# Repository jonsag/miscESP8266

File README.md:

# misc ESP8266

Tests and minor projects

## esp-01_ch340g

To program  

* Insert in programmer board  
* Hold down flash button
* Toggle reset button  
* Release flash button

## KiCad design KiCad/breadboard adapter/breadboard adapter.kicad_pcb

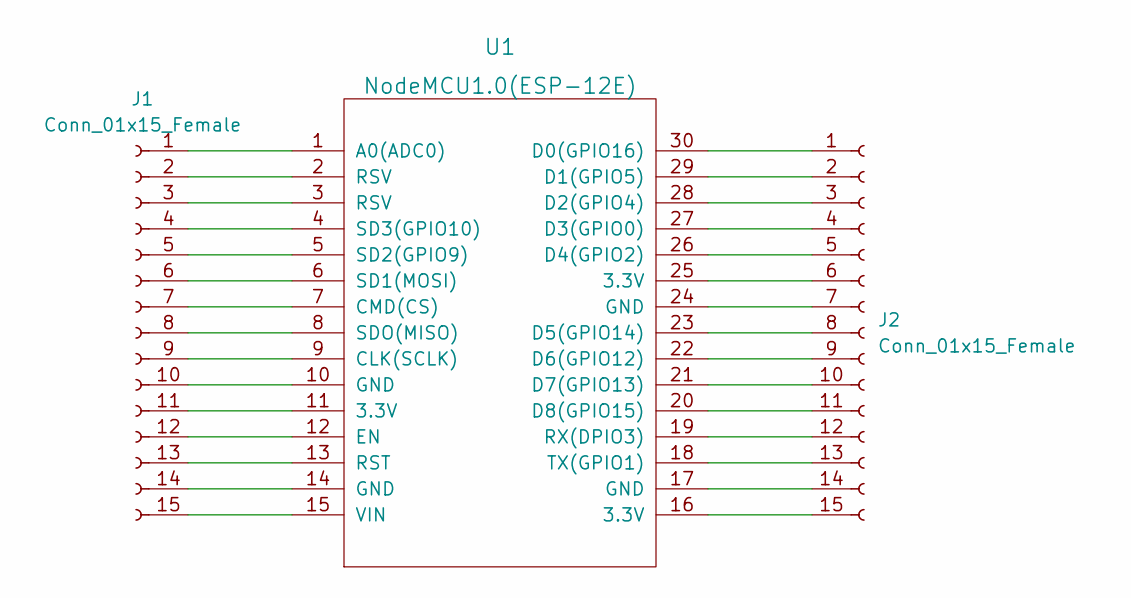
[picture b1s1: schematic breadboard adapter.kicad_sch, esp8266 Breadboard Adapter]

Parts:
J1, J2: Conn_01x15_Female; PinHeader_1x15_P2.54mm_Vertical
U1: NodeMCU1.0(ESP-12E); NodeMCU-LoLinV3_w_pinsockets_large

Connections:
unnamed: J1.1, U1.1 (A0(ADC0))
unnamed: J1.2, U1.2 (RSV)
unnamed: J1.3, U1.3 (RSV)
unnamed: J1.4, U1.4 (SD3(GPIO10))
unnamed: J1.5, U1.5 (SD2(GPIO9))
unnamed: J1.6, U1.6 (SD1(MOSI))
unnamed: J1.7, U1.7 (CMD(CS))
unnamed: J1.8, U1.8 (SDO(MISO))
unnamed: J1.9, U1.9 (CLK(SCLK))
unnamed: J1.10, U1.10 (GND)
unnamed: J1.11, U1.11 (3.3V)
unnamed: J1.12, U1.12 (EN)
unnamed: J1.13, U1.13 (RST)
unnamed: J1.14, U1.14 (GND)
unnamed: J1.15, U1.15 (VIN)
unnamed: J2.1, U1.30 (D0(GPIO16))
unnamed: J2.2, U1.29 (D1(GPIO5))
unnamed: J2.3, U1.28 (D2(GPIO4))
unnamed: J2.4, U1.27 (D3(GPIO0))
unnamed: J2.5, U1.26 (D4(GPIO2))
unnamed: J2.6, U1.25 (3.3V)
unnamed: J2.7, U1.24 (GND)
unnamed: J2.8, U1.23 (D5(GPIO14))
unnamed: J2.9, U1.22 (D6(GPIO12))
unnamed: J2.10, U1.21 (D7(GPIO13))
unnamed: J2.11, U1.20 (D8(GPIO15))
unnamed: J2.12, U1.19 (RX(DPIO3))
unnamed: J2.13, U1.18 (TX(GPIO1))
unnamed: J2.14, U1.17 (GND)
unnamed: J2.15, U1.16 (3.3V)

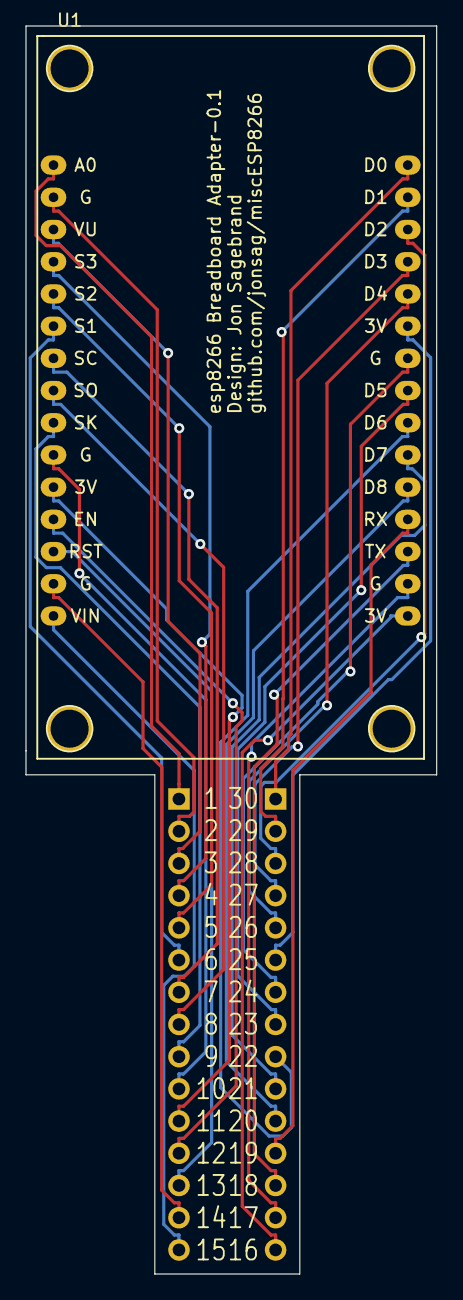
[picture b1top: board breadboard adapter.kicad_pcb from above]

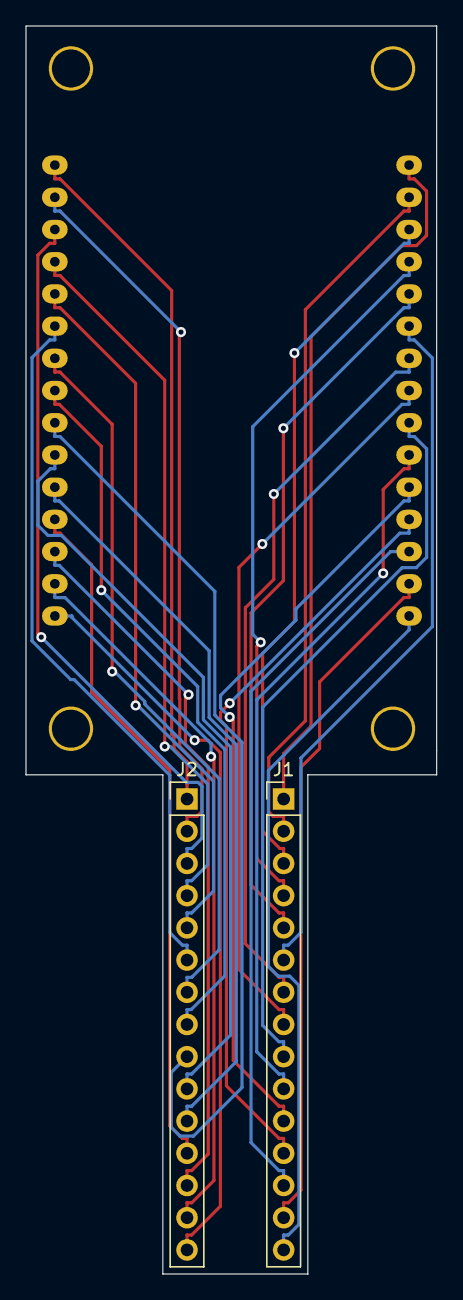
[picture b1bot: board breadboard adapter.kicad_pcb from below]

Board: 2 copper layers, 32.4 x 98.4 mm, 3 parts (2 on the bottom side), 30 nets.

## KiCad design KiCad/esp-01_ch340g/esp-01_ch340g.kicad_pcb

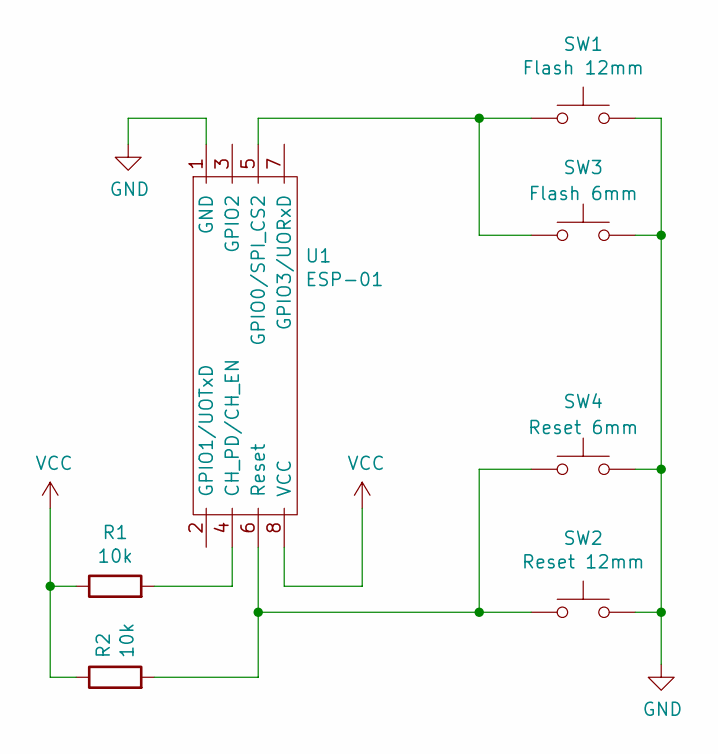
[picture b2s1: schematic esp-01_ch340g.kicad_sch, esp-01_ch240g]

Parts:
R1, R2: 10k; R_Axial_DIN0207_L6.3mm_D2.5mm_P10.16mm_Horizontal_larger_pa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
SW1: Flash 12mm; SW_PUSH-12mm_large
SW2: Reset 12mm; SW_PUSH-12mm_large
SW3: Flash 6mm; SW_PUSH_6mm_large
SW4: Reset 6mm; SW_PUSH_6mm_large
U1: ESP-01; ESP-01_w_pin_socket_large

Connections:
GND: SW1.2, SW2.2, SW3.2, SW4.2, U1.1 (GND)
unnamed: R1.2, U1.4 (CH_PD/CH_EN)
unnamed: R2.2, SW2.1, SW4.1, U1.6 (Reset)
unnamed: SW1.1, SW3.1, U1.5 (GPIO0/SPI_CS2)
VCC: R1.1, R2.1, U1.8 (VCC)

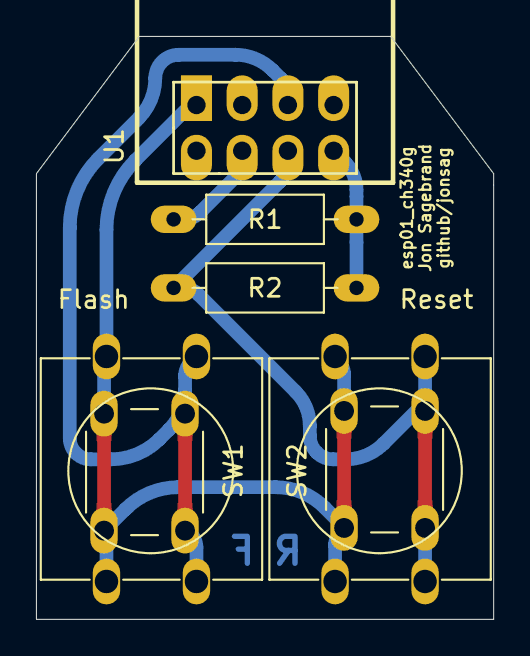
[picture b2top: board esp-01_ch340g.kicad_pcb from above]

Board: 2 copper layers, 25.4 x 32.4 mm, 7 parts (0 on the bottom side), 5 nets.

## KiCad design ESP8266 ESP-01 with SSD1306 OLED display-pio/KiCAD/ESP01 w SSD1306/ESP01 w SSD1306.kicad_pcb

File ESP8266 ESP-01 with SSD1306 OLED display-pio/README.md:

# Links

[https://simple-circuit.com/esp-01-esp8266-ssd1306-oled-i2c-mode/](ESP8266 ESP-01 with SSD1306 OLED display)
[https://richard-ramos.github.io/esp-01-oled/](Adding a OLED screen to the ESP-01)

[http://javl.github.io/image2cpp/](image2cpp)

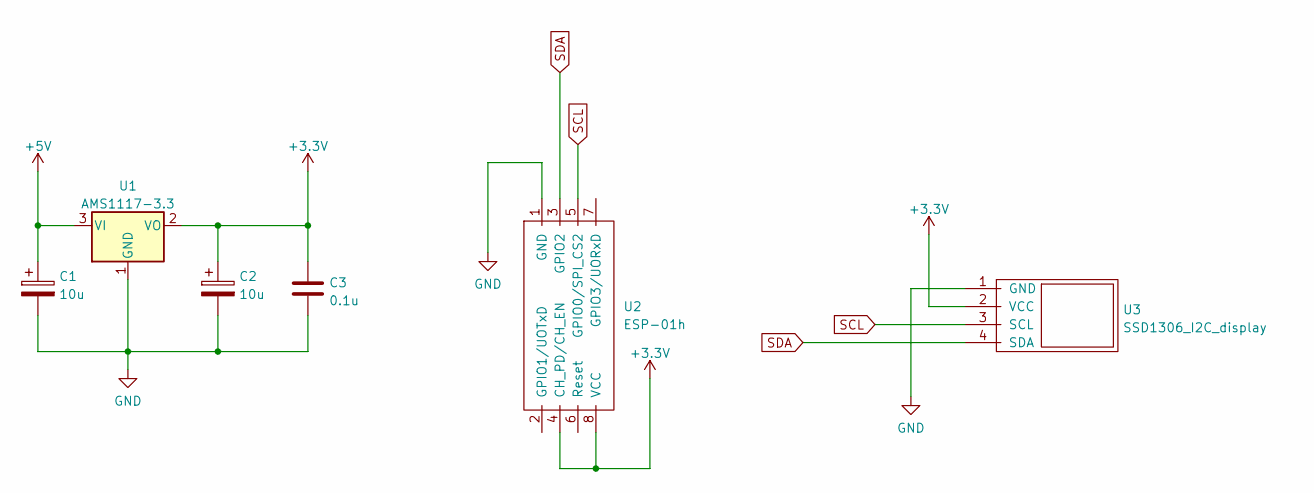
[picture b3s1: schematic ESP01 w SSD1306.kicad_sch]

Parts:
C1, C2: 10u; CP_Radial_D5.0mm_P2.00mm_larger
C3: 0.1u; C_Disc_D3.0mm_W1.6mm_P2.50mm_larg
U1: AMS1117-3.3; SOT-223-3_TabPin2
U2: ESP-01h; ESP-01_w_pin_socket_large
U3: SSD1306_I2C_display; SSD1306_I2C_0.96_OLED_display_large

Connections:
+3V3: C2.1, C3.1, U1.2 (VO), U2.4 (CH_PD/CH_EN), U2.8 (VCC), U3.2 (VCC)
+5V: C1.1, U1.3 (VI)
GND: C1.2, C2.2, C3.2, U1.1 (GND), U2.1 (GND), U3.1 (GND)
SCL: U2.5 (GPIO0/SPI_CS2), U3.3 (SCL)
SDA: U2.3 (GPIO2), U3.4 (SDA)

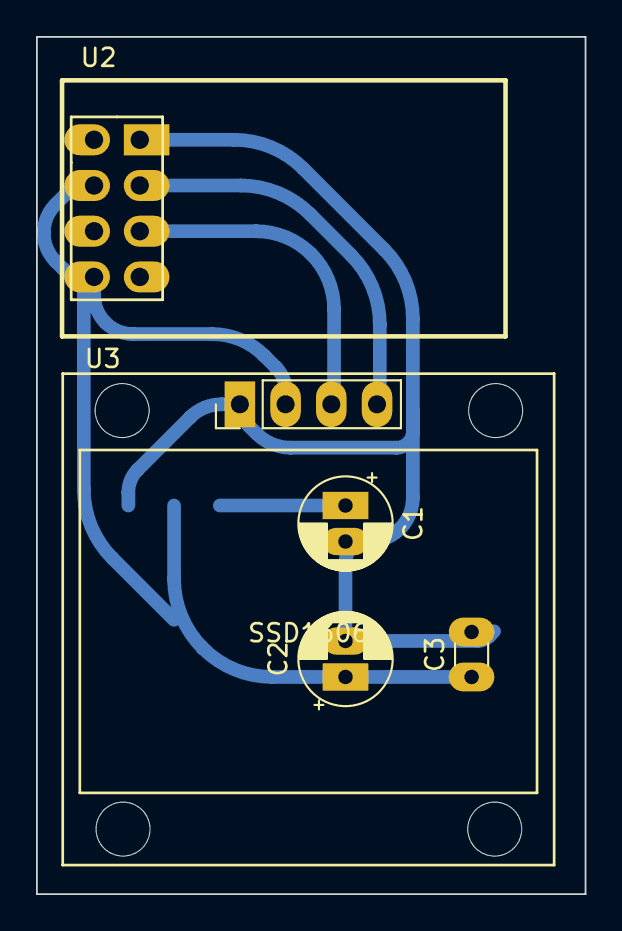
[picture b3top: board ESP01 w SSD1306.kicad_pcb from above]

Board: 2 copper layers, 30.5 x 47.6 mm, 6 parts (1 on the bottom side), 5 nets.

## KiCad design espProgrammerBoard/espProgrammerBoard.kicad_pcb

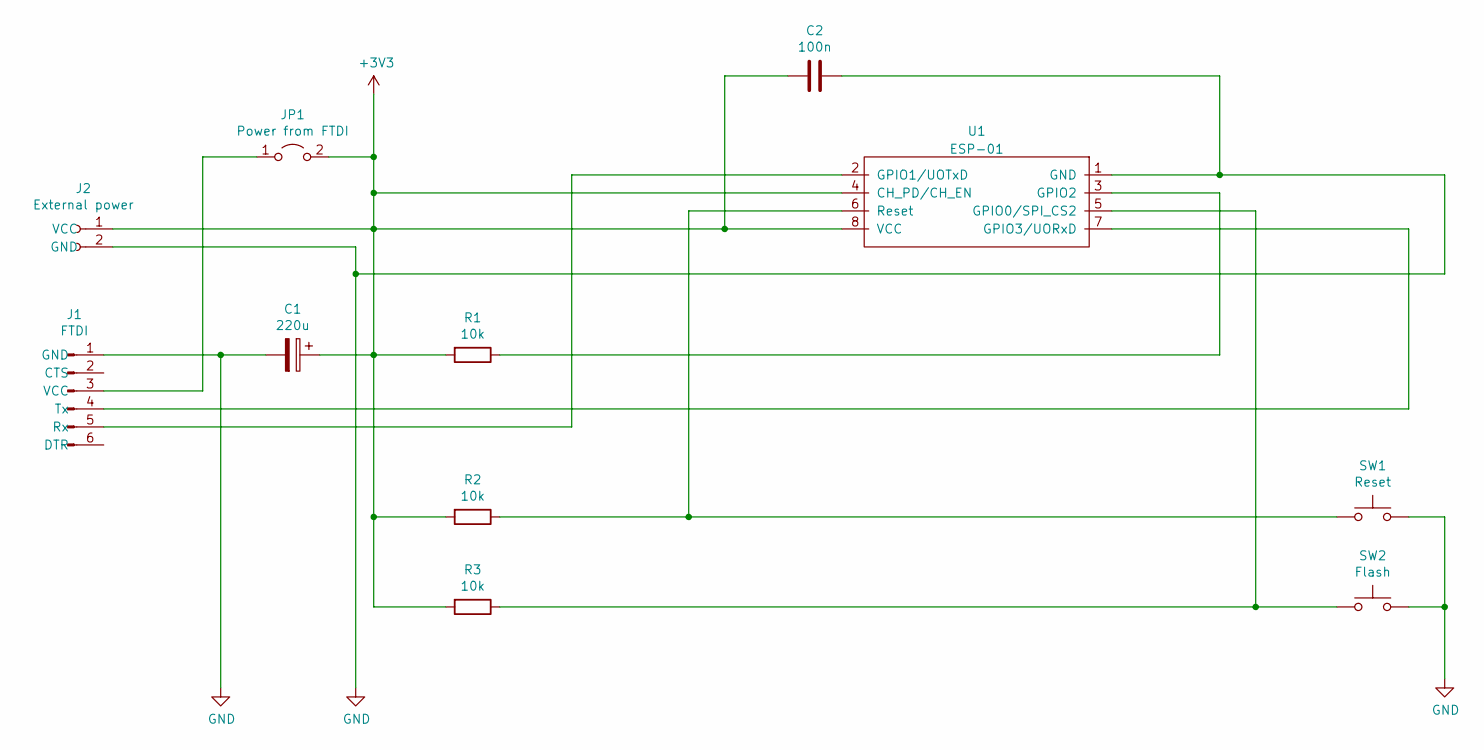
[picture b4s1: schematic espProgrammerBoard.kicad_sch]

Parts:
C1: 220u; CP_Radial_D6.3mm_P2.50mm_large
C2: 100n; C_Disc_D3.0mm_W1.6mm_P2.50mm_larg
J1: FTDI; 6-pin_FTDI_header_large
J2: External power; 2-pin_power_input_header_larger_pads
JP1: Power from FTDI; Jumper_1x02_P2.54mm_large
R1, R2, R3: 10k; R_Axial_DIN0207_L6.3mm_D2.5mm_P10.16mm_Horizontal_larger_pa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
SW1: Reset; SW_PUSH_6mm_large
SW2: Flash; SW_PUSH_6mm_large
U1: ESP-01; ESP-01_w_pin_socket_large

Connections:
+3V3: C1.1, C2.1, J2.1 (VCC), JP1.2 (B), R1.2, R2.2, R3.2, U1.4 (CH_PD/CH_EN), U1.8 (VCC)
GND: C1.2, C2.2, J1.1 (GND), J2.2 (GND), SW1.2, SW2.2, U1.1 (GND)
unnamed: J1.3 (VCC), JP1.1 (A)
unnamed: J1.4 (Tx), U1.7 (GPIO3/UORxD)
unnamed: J1.5 (Rx), U1.2 (GPIO1/UOTxD)
unnamed: R1.1, U1.3 (GPIO2)
unnamed: R2.1, SW1.1, U1.6 (Reset)
unnamed: R3.1, SW2.1, U1.5 (GPIO0/SPI_CS2)

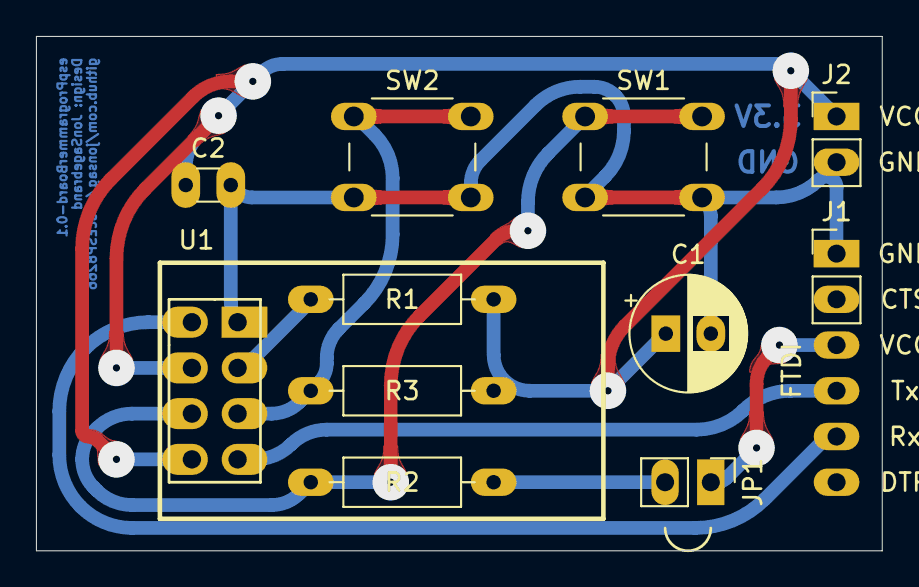
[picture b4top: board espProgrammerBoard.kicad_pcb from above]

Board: 2 copper layers, 47.0 x 28.6 mm, 11 parts (0 on the bottom side), 8 nets.

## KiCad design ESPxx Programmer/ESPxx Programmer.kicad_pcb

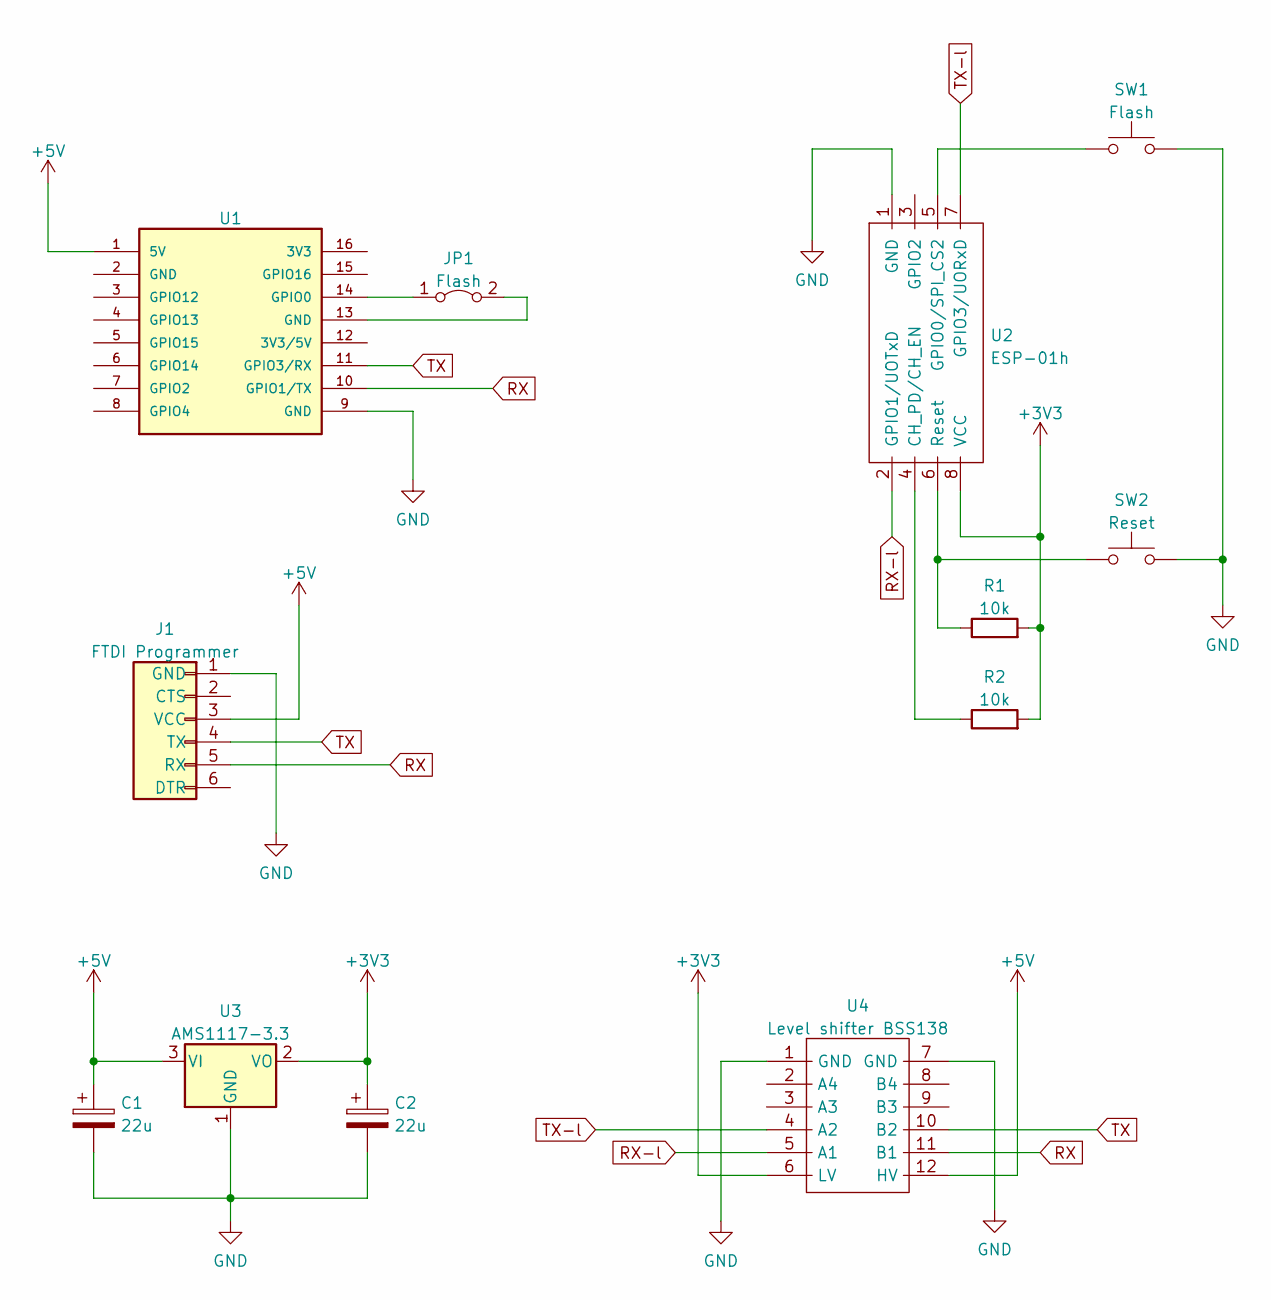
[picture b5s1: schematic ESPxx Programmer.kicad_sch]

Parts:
C1, C2: 22u; CP_Radial_D5.0mm_P2.00mm_larger
J1: FTDI Programmer; 6-pin FTDI Programmer PinSocket large
JP1: Flash; Jumper_1x02_P2.54mm_large
R1, R2: 10k; R_Axial_DIN0207_L6.3mm_D2.5mm_P10.16mm_Horizontal_larger_pa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
SW1: Flash; SW_PUSH-12mm_large
SW2: Reset; SW_PUSH-12mm_large
U1: ESP32-CAM
U2: ESP-01h; ESP-01_w_pin_socket_large
U3: AMS1117-3.3; SOT-223-3_TabPin2
U4: Level shifter BSS138; 4-channel_I2C_level_shifter_BSS138_large

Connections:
+3V3: C2.1, R1.2, R2.2, U2.8 (VCC), U3.2 (VO), U4.6 (LV)
+5V: C1.1, J1.3 (VCC), U1.1 (5V), U3.3 (VI), U4.12 (HV)
GND: C1.2, C2.2, J1.1 (GND), SW1.2, SW2.2, U1.9 (GND), U2.1 (GND), U3.1 (GND), U4.1 (GND), U4.7 (GND)
unnamed: JP1.1 (A), U1.14 (GPIO0)
unnamed: JP1.2 (B), U1.13 (GND)
unnamed: R1.1, SW2.1, U2.6 (Reset)
unnamed: R2.1, U2.4 (CH_PD/CH_EN)
unnamed: SW1.1, U2.5 (GPIO0/SPI_CS2)
RX: J1.5 (RX), U1.10 (GPIO1/TX), U4.11 (B1)
RX-l: U2.2 (GPIO1/UOTxD), U4.5 (A1)
TX: J1.4 (TX), U1.11 (GPIO3/RX), U4.10 (B2)
TX-l: U2.7 (GPIO3/UORxD), U4.4 (A2)

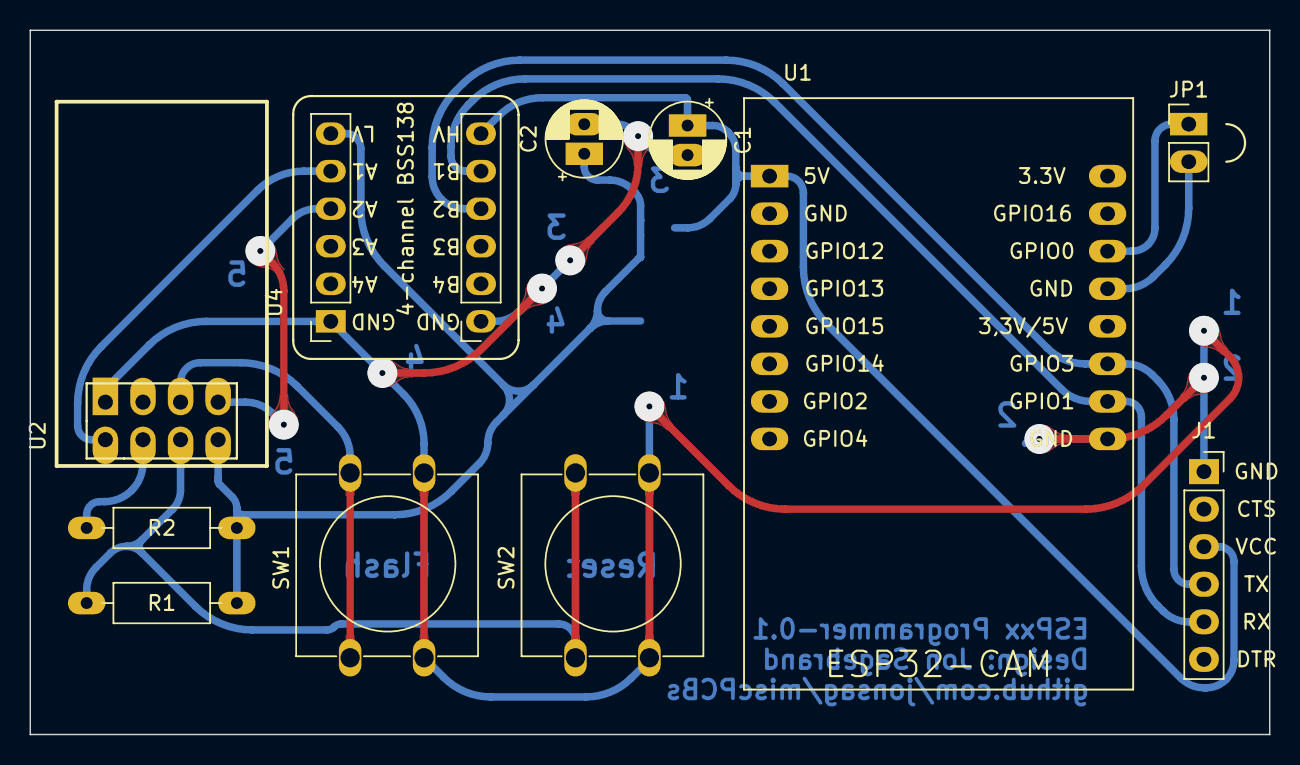
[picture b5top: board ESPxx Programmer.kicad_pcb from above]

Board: 2 copper layers, 83.8 x 47.6 mm, 12 parts (1 on the bottom side), 12 nets.

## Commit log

2022-04-23 readme
2022-04-24 kicad
2022-04-25 no success yet
2022-04-25 built from newer example
2022-04-26 tests
2022-04-26 works now
2022-04-26 now external libs
2022-06-12 esp w 1306
2022-09-18 page settings n espScale
2022-09-18 esp01
2022-09-18 AT firmware
2022-10-23 programmer boards
2022-10-23 page settings
2025-02-09 workspace
2025-02-09 kicad v8
2025-02-17 moves
2025-03-17 veroroute
